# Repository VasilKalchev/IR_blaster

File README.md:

# IR_blaster
Battery powered ATmega328 connected to an SPI device and 4 LEDs.

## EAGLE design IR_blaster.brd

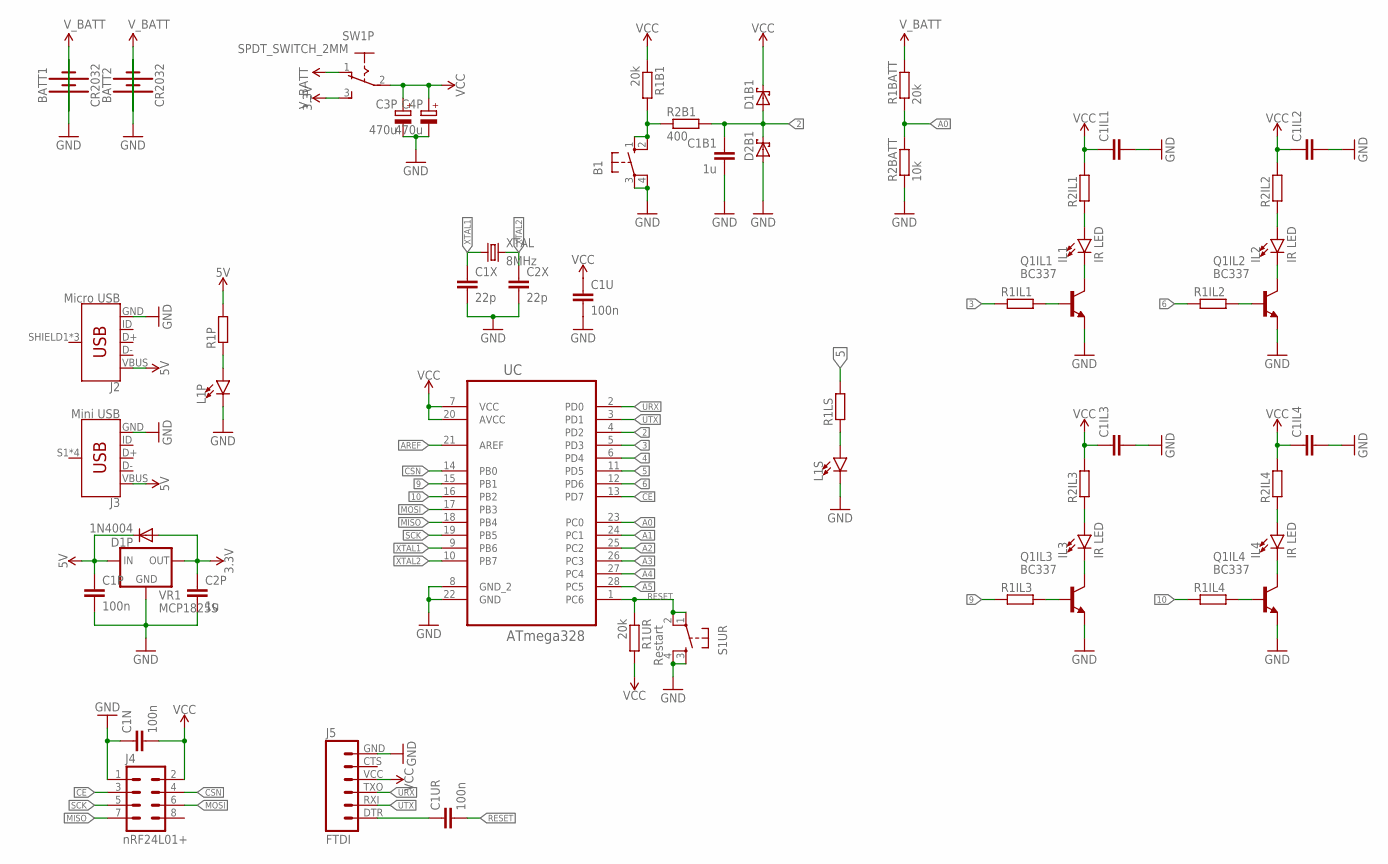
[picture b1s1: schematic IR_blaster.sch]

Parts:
B1: 40-XX; B3F-40XX
BATT1, BATT2: CR2032; BATTCOM_20MM_PTH
C1B1, C2P: 1u; C050-050X075
C1IL1, C1IL2, C1IL3, C1IL4: C-EU050-050X075; C050-050X075
C1N: 100n; C025-025X050
C1P, C1U, C1UR: 100n; C050-025X075
C1X, C2X: 22p; C025-025X050
C3P, C4P: 470u; E5-8,5
D1B1, D2B1: SCHOTTKY-DIODEDO41-7; DO41-7
D1P: 1N4004; DO41-10
IL1, IL2, IL3, IL4: IR LED; LED_5MM
J2: Micro USB; USB-B-MICRO-SMD
J3: Mini USB; USB-MINIB
J4: nRF24L01+; 2X4; MPN MOD-NRF24LR
J5: FTDI; FTDI_BASIC
L1P, L1S: LED3MM; LED_3MM
Q1IL1, Q1IL2, Q1IL3, Q1IL4: BC337; TO92
R1B1, R1BATT, R1UR: 20k; 0207/7
R1IL1, R1IL2, R1IL3, R1IL4, R1LS, R1P, R2IL1, R2IL2, R2IL3, R2IL4: R-EU_0207/7; 0207/7
R2B1: 400; 0207/7
R2BATT: 10k; 0207/7
S1UR: Restart; TACTILE-PTH
SW1P: SPDT_SWITCH_2MM; SWITCH_2MM
UC: ATmega328; DIP254P762X457-28
VR1: MCP1825S; 78XXL
XTAL: 8MHz; HC49/S

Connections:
2: C1B1.1, D1B1.A, D2B1.C, R2B1.2, UC.4 (PD2)
3: R1IL1.1, UC.5 (PD3)
3.3V: C2P.1, D1P.A, SW1P.3, VR1.OUT
4: UC.6 (PD4)
5: R1LS.2, UC.11 (PD5)
5V: C1P.1, D1P.C, J2.VBUS, J3.VBUS, R1P.2, VR1.IN
6: R1IL2.1, UC.12 (PD6)
9: R1IL3.1, UC.15 (PB1)
10: R1IL4.1, UC.16 (PB2)
A0: R1BATT.1, R2BATT.2, UC.23 (PC0)
A1: UC.24 (PC1)
A2: UC.25 (PC2)
A3: UC.26 (PC3)
A4: UC.27 (PC4)
A5: UC.28 (PC5)
AREF: UC.21 (AREF)
CE: J4.3, UC.13 (PD7)
CSN: J4.4, UC.14 (PB0)
GND: B1.3, B1.4 (P1), BATT1.2 (-), BATT2.2 (-), C1B1.2, C1IL1.2, C1IL2.2, C1IL3.2, C1IL4.2, C1N.1, C1P.2, C1U.2, C1X.2, C2P.2, C2X.2, C3P.-, C4P.-, D2B1.A, J2.GND, J3.GND, J4.1, J5.GND (6), L1P.K (C), L1S.K (C), Q1IL1.1 (E), Q1IL2.1 (E), Q1IL3.1 (E), Q1IL4.1 (E), R2BATT.1, S1UR.3, S1UR.4, UC.8 (GND_2), UC.22 (GND), VR1.GND
MISO: J4.7, UC.18 (PB4)
MOSI: J4.6, UC.17 (PB3)
unnamed: L1S.A, R1LS.1
unnamed: L1P.A, R1P.1
unnamed: IL1.K (C), Q1IL1.3 (C)
unnamed: IL1.A, R2IL1.1
unnamed: Q1IL1.2 (B), R1IL1.2
unnamed: C1UR.1, J5.DTR (1)
unnamed: IL2.K (C), Q1IL2.3 (C)
unnamed: IL2.A, R2IL2.1
unnamed: Q1IL2.2 (B), R1IL2.2
unnamed: IL3.K (C), Q1IL3.3 (C)
unnamed: IL3.A, R2IL3.1
unnamed: Q1IL3.2 (B), R1IL3.2
unnamed: IL4.K (C), Q1IL4.3 (C)
unnamed: IL4.A, R2IL4.1
unnamed: Q1IL4.2 (B), R1IL4.2
unnamed: B1.1 (S), B1.2 (S1), R1B1.2, R2B1.1
RESET: C1UR.2, R1UR.1, S1UR.1, S1UR.2, UC.1 (PC6)
SCK: J4.5, UC.19 (PB5)
URX: J5.TXO (3), UC.2 (PD0)
UTX: J5.RXI (2), UC.3 (PD1)
VCC: C1IL1.1, C1IL2.1, C1IL3.1, C1IL4.1, C1N.2, C1U.1, C3P.+, C4P.+, D1B1.C, J4.2, J5.VCC (4), R1B1.1, R1UR.2, R2IL1.2, R2IL2.2, R2IL3.2, R2IL4.2, SW1P.2, UC.7 (VCC), UC.20 (AVCC)
V_BATT: BATT1.1 (+), BATT2.1 (+), R1BATT.2, SW1P.1
XTAL1: C1X.1, UC.9 (PB6), XTAL.1
XTAL2: C2X.1, UC.10 (PB7), XTAL.2

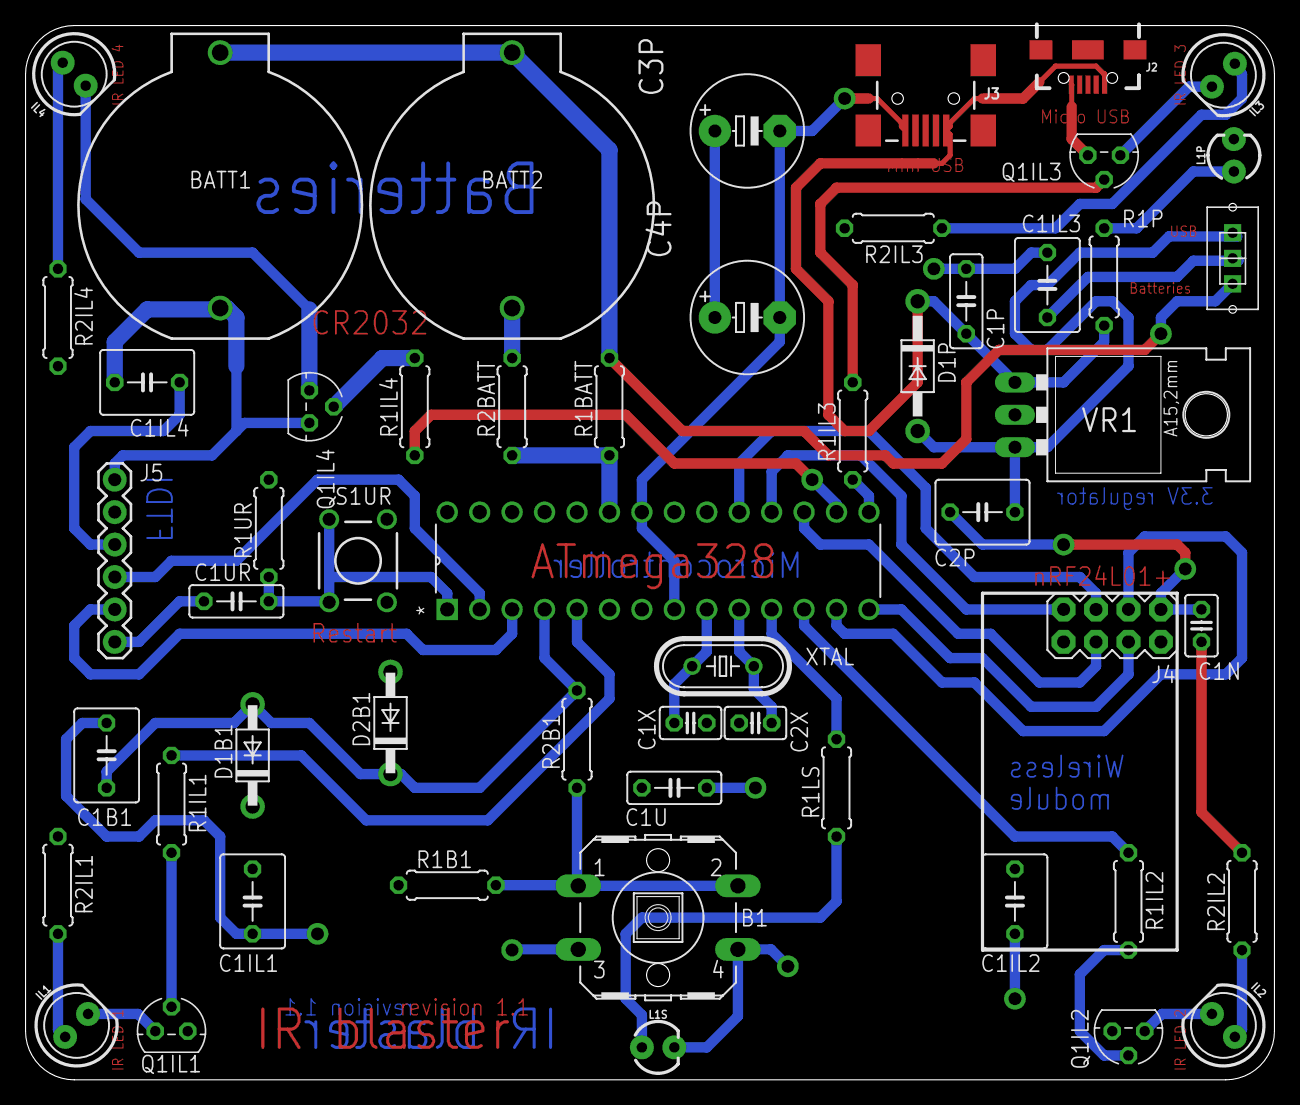
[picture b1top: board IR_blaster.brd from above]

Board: 2 copper layers, 97.8 x 82.5 mm, 54 parts (0 on the bottom side), 38 nets.

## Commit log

2017-05-01 :lollipop: Added .gitattributes & .gitignore files
2017-05-01 Expored images
2017-05-01 3d model
2017-05-02 Changed the batteries packages to double pin ones.
2017-05-05 Changed to smaller capacitors

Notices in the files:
parts and their libraries:
SparkFun-Connectors: Licensing: Creative Commons ShareAlike 4.0 International - https://creativecommons.org/licenses/by-sa/4.0
